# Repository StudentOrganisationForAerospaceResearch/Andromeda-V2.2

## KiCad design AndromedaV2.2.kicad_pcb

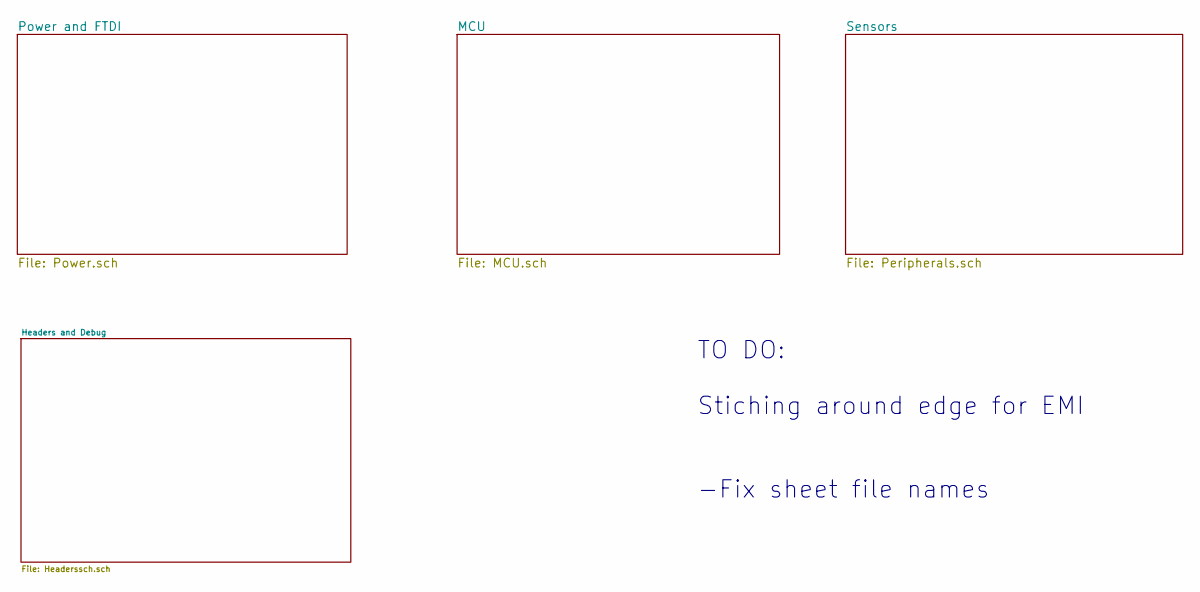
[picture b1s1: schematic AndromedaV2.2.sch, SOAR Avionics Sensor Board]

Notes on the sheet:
TO DO: Stiching around edge for EMI -Fix sheet file names

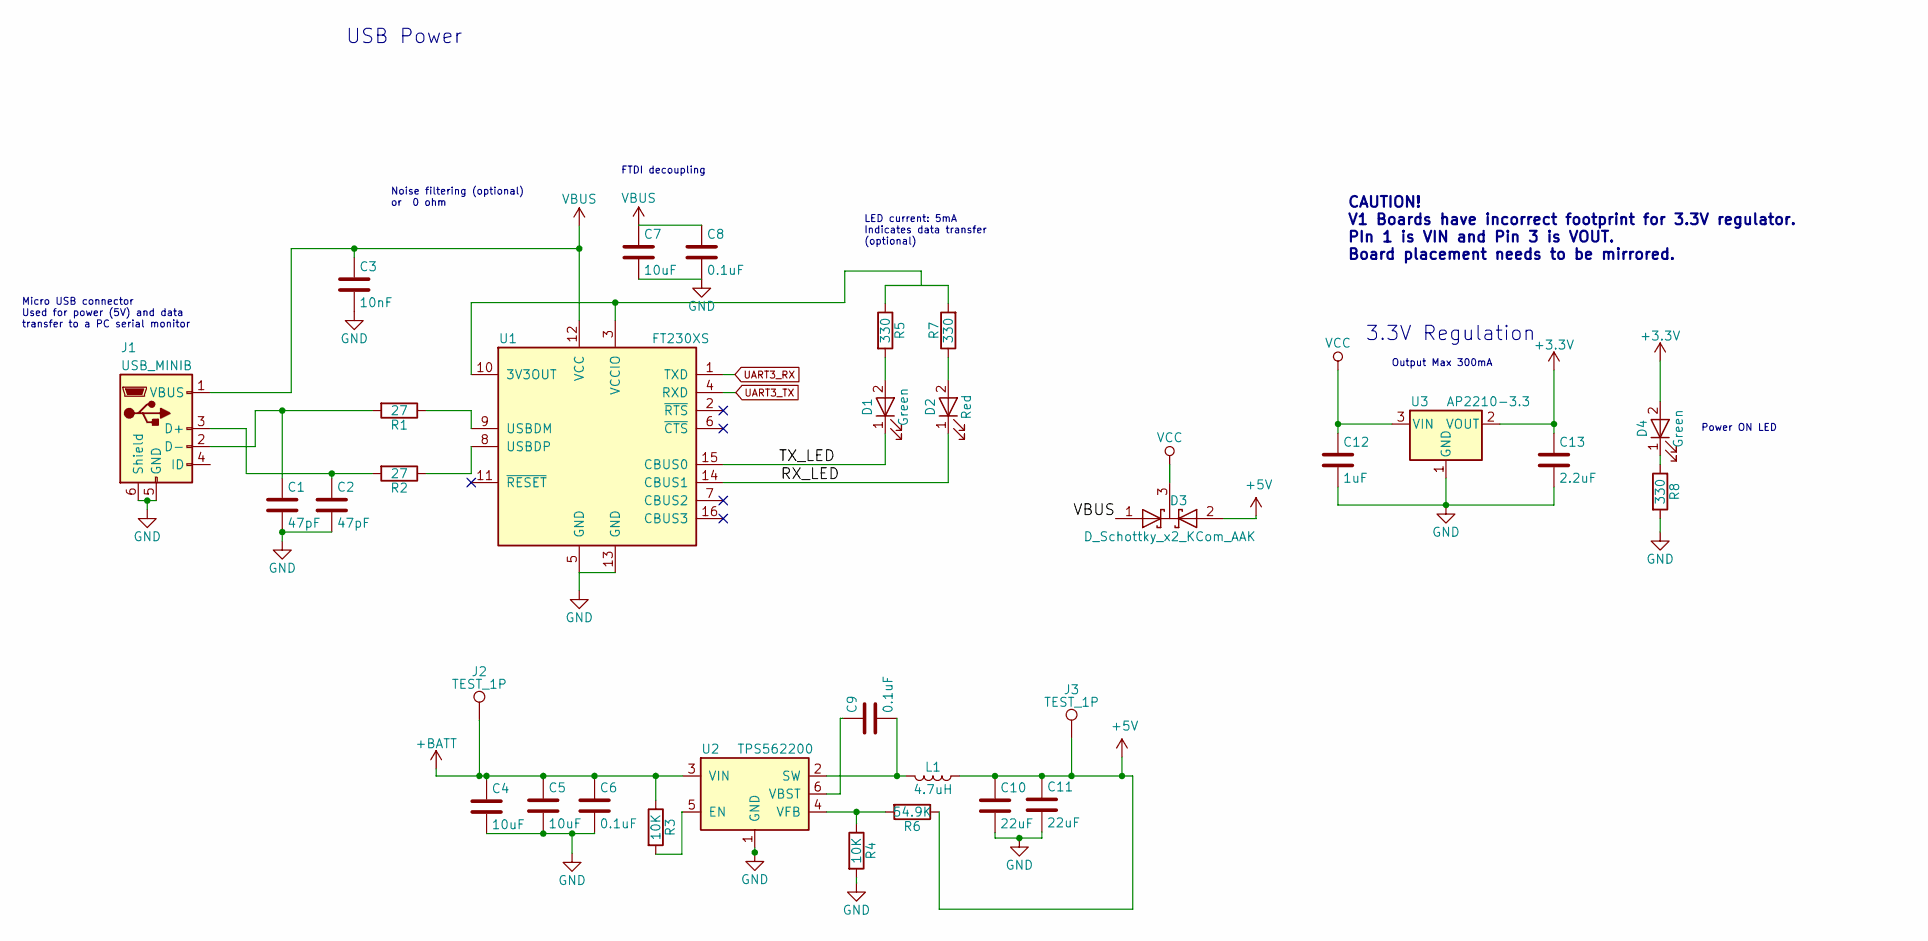
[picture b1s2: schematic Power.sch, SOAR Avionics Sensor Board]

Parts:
C1, C2: 47pF; C_0603
C3: 10nF; C_0603
C4, C5, C7: 10uF; C_0603
C6, C8, C9: 0.1uF; C_0603
C10, C11: 22uF; C_0603
C12: 1uF; C_0603
C13: 2.2uF; C_0603
D1, D4: Green; LED_0805_2012Metric; Digikey LG R971-KN-1
D2: Red; LED_0805_2012Metric; Digikey 475-1278-1-ND
D3: D_Schottky_x2_KCom_AAK; SOT-23; Digikey 1727-5188-1-ND
J1: USB_MINIB; USB-Mini-B; Digikey 690-005-299-043
J2, J3: TEST_1P; Test_Point_Pad_d1.5mm
L1: 4.7uH; L_1008
R1, R2: 27; R_0603
R3, R4: 10K; R_0603
R5, R7, R8: 330; R_0603
R6: 54.9K; R_0603
U1: FT230XS; SSOP-16_3.9x4.9mm_P0.635mm; Digikey 768-1135-1-ND
U2: TPS562200; SOT-23-6
U3: AP2210-3.3; SOT-23

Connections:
+3V3: C13.1, D4.2 (A), U3.2 (VOUT); also elsewhere on the board
+5V: C10.1, C11.1, D3.2 (A), J3.1, L1.1, R6.1; also elsewhere on the board
+BATT: C4.1, C5.1, C6.1, J2.1, R3.1, U2.3 (VIN); also elsewhere on the board
/Power and FTDI/RX_LED: D2.1 (K), U1.14 (CBUS1)
/Power and FTDI/TX_LED: D1.1 (K), U1.15 (CBUS0)
GND: C1.2, C2.2, C3.2, C4.2, C5.2, C6.2, C7.2, C8.2, C10.2, C11.2, C12.2, C13.2, J1.5 (GND), J1.6 (Shield), R4.2, R8.2, U1.5 (GND), U1.13 (GND), U2.1 (GND), U3.1 (GND); also elsewhere on the board
unnamed: C1.1, J1.2 (D-), R1.2
unnamed: C2.1, J1.3 (D+), R2.2
unnamed: C9.1, U2.6 (VBST)
unnamed: C9.2, L1.2, U2.2 (SW)
unnamed: D1.2 (A), R5.2
unnamed: D2.2 (A), R7.1
unnamed: D4.1 (K), R8.1
unnamed: R1.1, U1.9 (USBDM)
unnamed: R2.1, U1.8 (USBDP)
unnamed: R3.2, U2.5 (EN)
unnamed: R4.1, R6.2, U2.4 (VFB)
unnamed: R5.1, R7.2
unnamed: U1.3 (VCCIO), U1.10 (3V3OUT)
UART3_RX: U1.1 (TXD); also elsewhere on the board
UART3_TX: U1.4 (RXD); also elsewhere on the board
VBUS: C3.1, C7.1, C8.1, D3.1 (A), J1.1 (VBUS), U1.12 (VCC)
VCC: C12.1, D3.3 (K), U3.3 (VIN)

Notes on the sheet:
Output Max 300mA
Power ON LED
LED current: 5mA Indicates data transfer (optional)
Micro USB connector Used for power (5V) and data transfer to a PC serial monitor
Noise filtering (optional) or 0 ohm
FTDI decoupling
USB Power
3.3V Regulation
CAUTION! V1 Boards have incorrect footprint for 3.3V regulator. PIn 1 is VIN and Pin 3 is VOUT. Board placement needs to be mirrored.

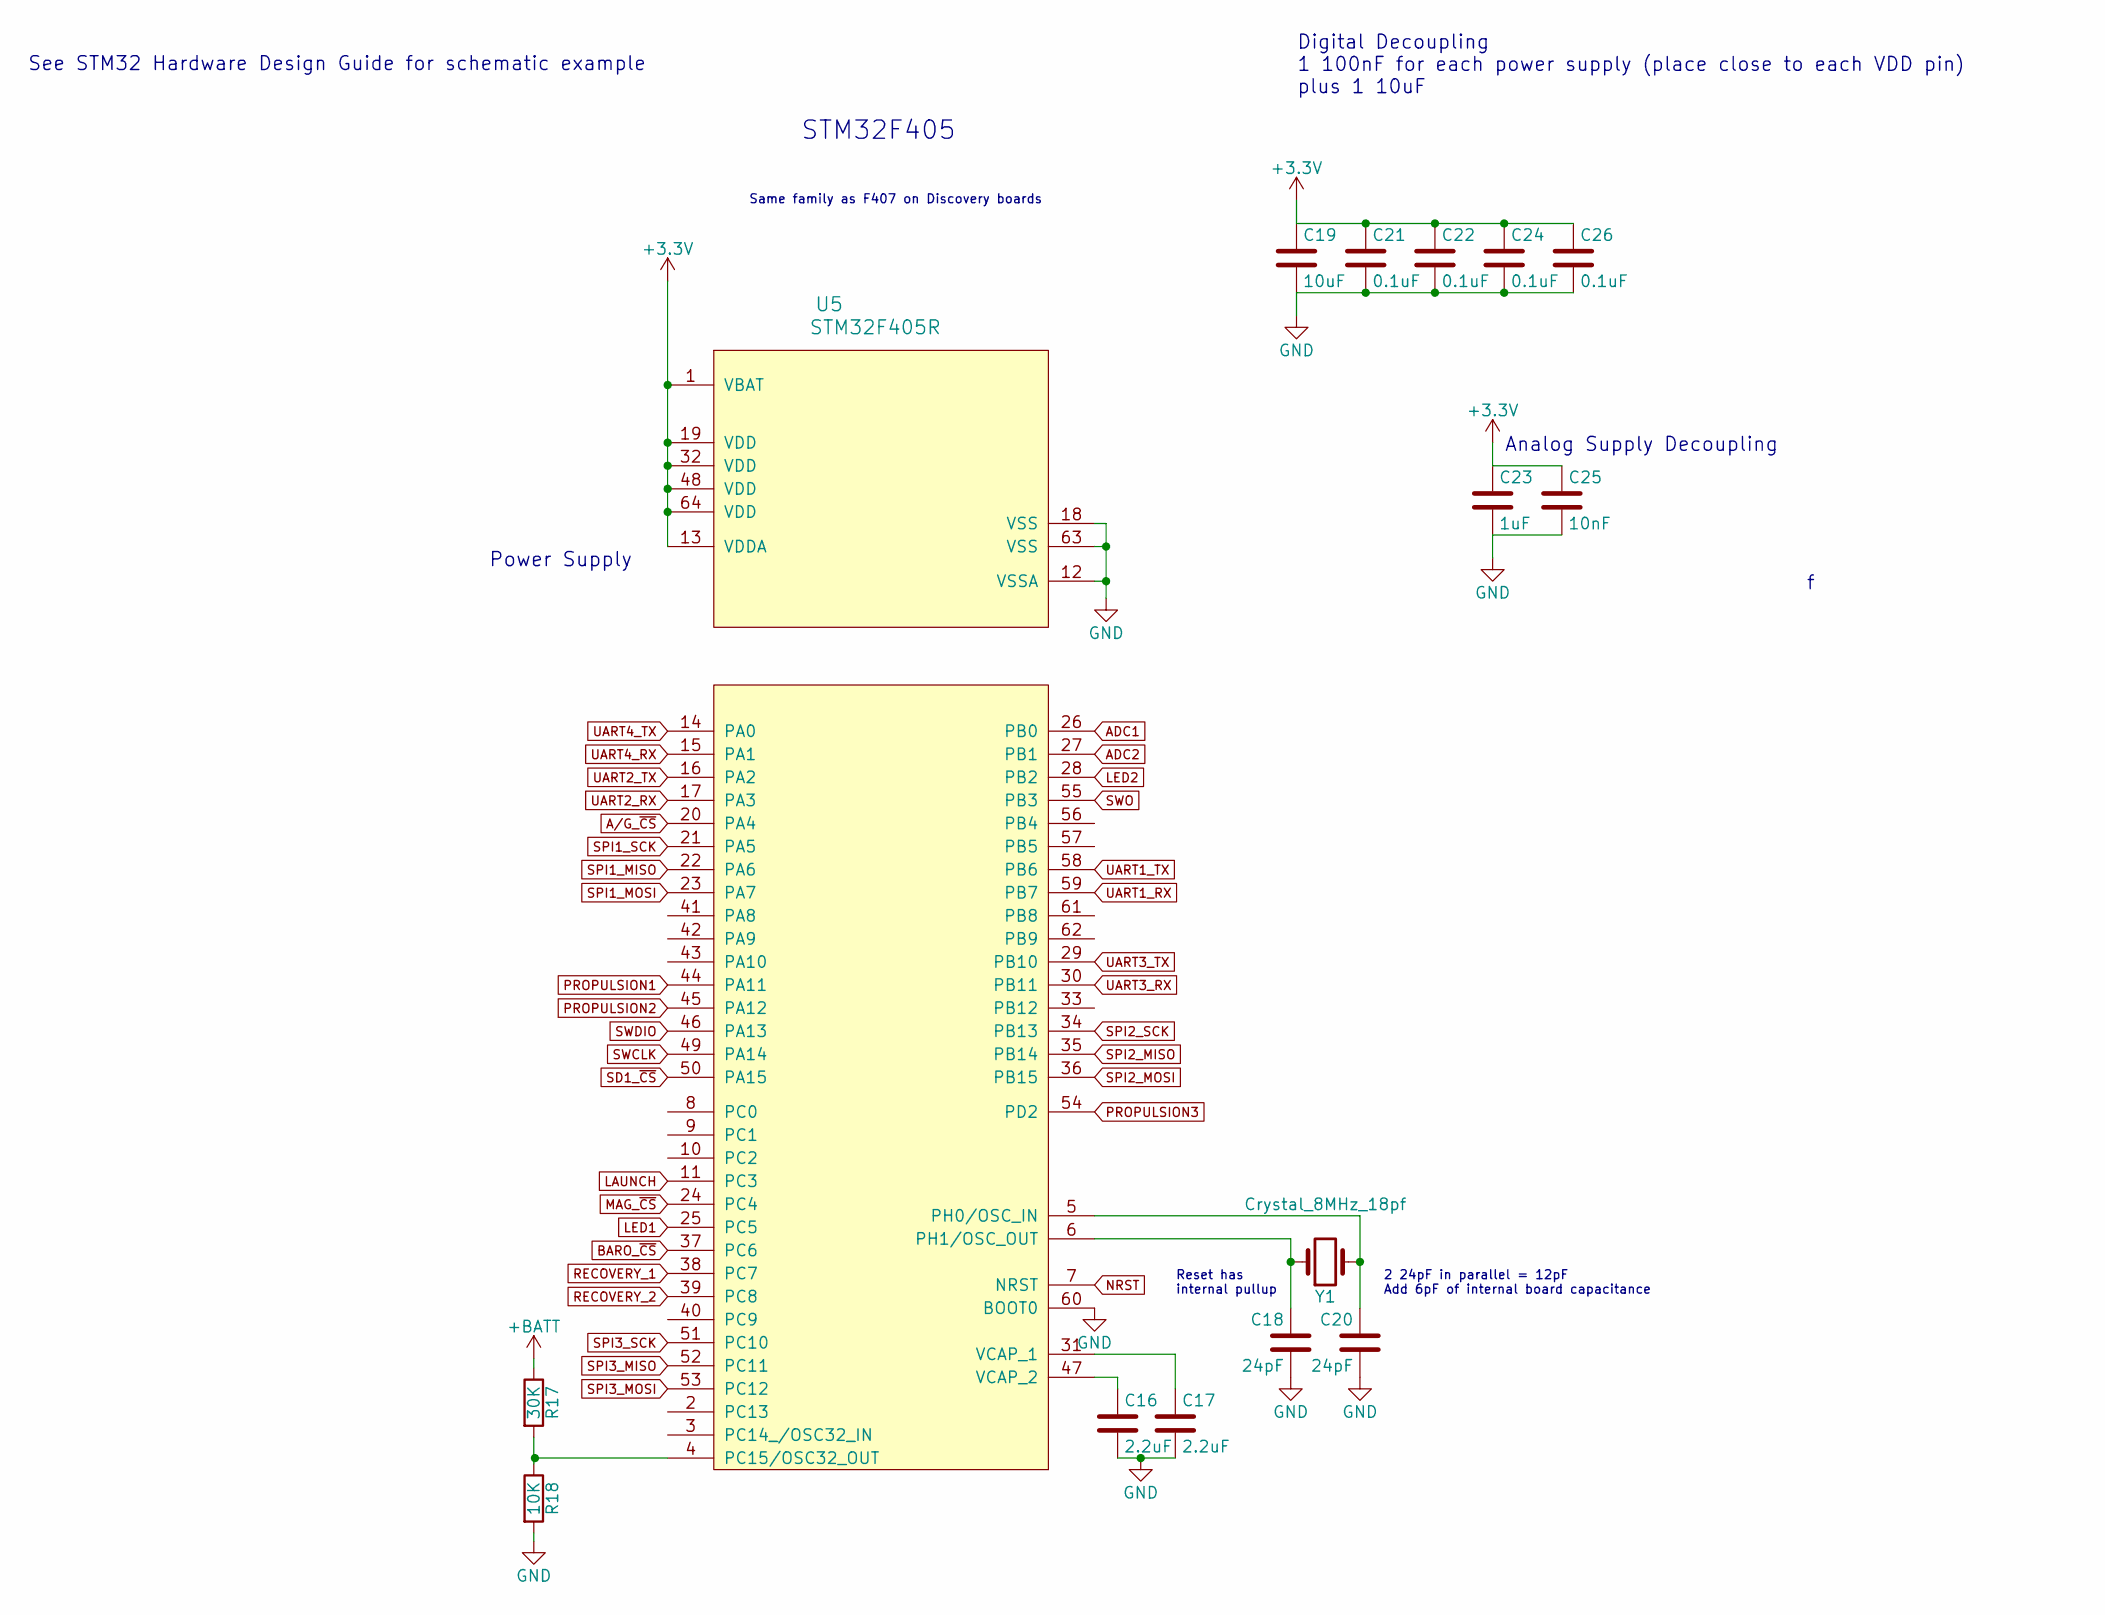
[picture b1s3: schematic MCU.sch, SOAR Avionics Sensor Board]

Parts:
C16, C17: 2.2uF; C_0603
C18, C20: 24pF; C_0603
C19: 10uF; C_0603
C21, C22, C24, C26: 0.1uF; C_0603
C23: 1uF; C_0603
C25: 10nF; C_0603
R17: 30K; R_0603
R18: 10K; R_0603
U5: STM32F405R; LQFP-64_10x10mm_P0.5mm; Digikey 497-11767-ND
Y1: Crystal_8MHz_18pf; Crystal_SMD_HC49-SD; Digikey 535-9089-1-ND

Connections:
+3V3: C19.1, C21.1, C22.1, C23.1, C24.1, C25.1, C26.1, U5.1 (VBAT), U5.13 (VDDA), U5.19 (VDD), U5.32 (VDD), U5.48 (VDD), U5.64 (VDD); also elsewhere on the board
+BATT: R17.1; also elsewhere on the board
A/G_~CS: U5.20 (PA4); also elsewhere on the board
ADC1: U5.26 (PB0); also elsewhere on the board
ADC2: U5.27 (PB1); also elsewhere on the board
BARO_~CS: U5.37 (PC6); also elsewhere on the board
GND: C16.2, C17.2, C18.2, C19.2, C20.2, C21.2, C22.2, C23.2, C24.2, C25.2, C26.2, R18.2, U5.12 (VSSA), U5.18 (VSS), U5.60 (BOOT0), U5.63 (VSS); also elsewhere on the board
LAUNCH: U5.11 (PC3); also elsewhere on the board
LED1: U5.25 (PC5); also elsewhere on the board
LED2: U5.28 (PB2); also elsewhere on the board
MAG_~CS: U5.24 (PC4); also elsewhere on the board
NRST: U5.7 (NRST); also elsewhere on the board
unnamed: C16.1, U5.47 (VCAP_2)
unnamed: C17.1, U5.31 (VCAP_1)
unnamed: C18.1, U5.6 (PH1/OSC_OUT), Y1.1
unnamed: C20.1, U5.5 (PH0/OSC_IN), Y1.2
unnamed: R17.2, R18.1, U5.4 (PC15/OSC32_OUT)
PROPULSION1: U5.44 (PA11); also elsewhere on the board
PROPULSION2: U5.45 (PA12); also elsewhere on the board
PROPULSION3: U5.54 (PD2); also elsewhere on the board
RECOVERY_1: U5.38 (PC7); also elsewhere on the board
RECOVERY_2: U5.39 (PC8); also elsewhere on the board
SD1_~CS: U5.50 (PA15); also elsewhere on the board
SPI1_MISO: U5.22 (PA6); also elsewhere on the board
SPI1_MOSI: U5.23 (PA7); also elsewhere on the board
SPI1_SCK: U5.21 (PA5); also elsewhere on the board
SPI2_MISO: U5.35 (PB14); also elsewhere on the board
SPI2_MOSI: U5.36 (PB15); also elsewhere on the board
SPI2_SCK: U5.34 (PB13); also elsewhere on the board
SPI3_MISO: U5.52 (PC11); also elsewhere on the board
SPI3_MOSI: U5.53 (PC12); also elsewhere on the board
SPI3_SCK: U5.51 (PC10); also elsewhere on the board
SWCLK: U5.49 (PA14); also elsewhere on the board
SWDIO: U5.46 (PA13); also elsewhere on the board
SWO: U5.55 (PB3); also elsewhere on the board
UART1_RX: U5.59 (PB7); also elsewhere on the board
UART1_TX: U5.58 (PB6); also elsewhere on the board
UART2_RX: U5.17 (PA3); also elsewhere on the board
UART2_TX: U5.16 (PA2); also elsewhere on the board
UART3_RX: U5.30 (PB11); also elsewhere on the board
UART3_TX: U5.29 (PB10); also elsewhere on the board
UART4_RX: U5.15 (PA1); also elsewhere on the board
UART4_TX: U5.14 (PA0); also elsewhere on the board

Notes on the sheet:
Reset has internal pullup
Digital Decoupling 1 100nF for each power supply (place close to each VDD pin) plus 1 10uF
Analog Supply Decoupling
See STM32 Hardware Design Guide for schematic example
Power Supply
2 24pF in parallel = 12pF Add 6pF of internal board capacitance
STM32F405
Same family as F407 on Discovery boards

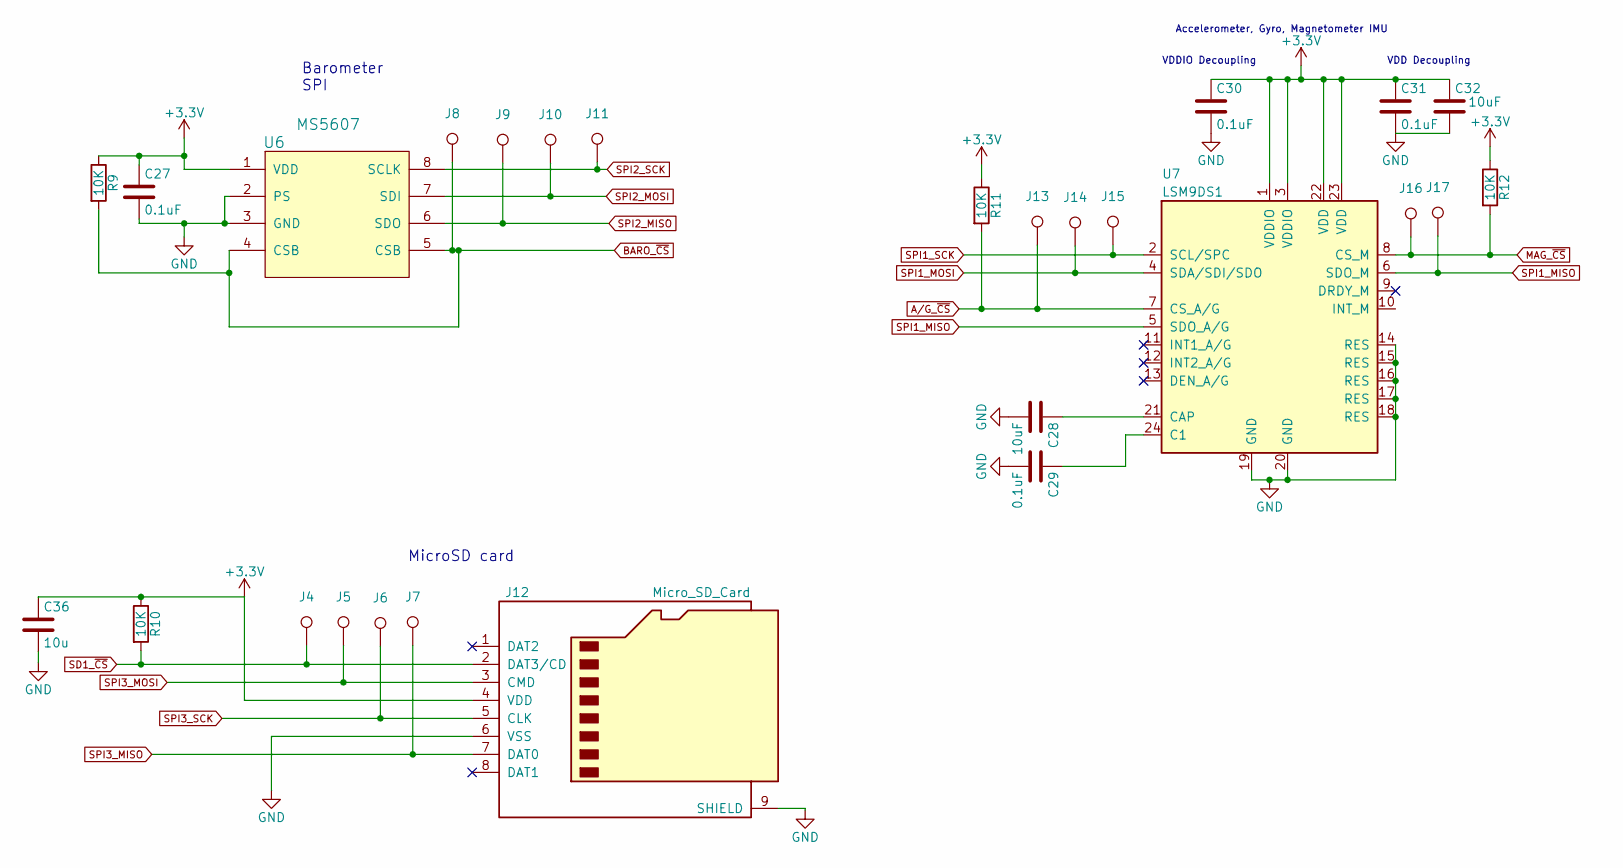
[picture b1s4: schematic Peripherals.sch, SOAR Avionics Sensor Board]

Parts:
C27, C29, C30, C31: 0.1uF; C_0603
C28, C32: 10uF; C_0603
C36: 10u; C_0603
J4, J5, J6, J7, J8, J9, J10, J11, J13, J14, J15, J16, J17: TEST_1P; Test_Point_Pad_d1.5mm
J12: Micro_SD_Card; Hirose_DM3AT-SF-PEJM5_MicroSD; Digikey 0472192001
R9, R10, R11, R12: 10K; R_0603
U6: MS5607; LGA-8_3x5mm_P1.25mm; Digikey MS560702BA03-00
U7: LSM9DS1; LGA-24L_3x3.5mm_P0.43mm; Digikey 497-14946-1-ND

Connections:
+3V3: C27.1, C30.1, C31.1, C32.1, C36.1, J12.4 (VDD), R9.1, R10.1, R11.1, R12.1, U6.1 (VDD), U7.1 (VDDIO), U7.3 (VDDIO), U7.22 (VDD), U7.23 (VDD); also elsewhere on the board
A/G_~CS: J13.1, R11.2, U7.7 (CS_A/G); also elsewhere on the board
BARO_~CS: J8.1, R9.2, U6.4 (CSB), U6.5 (CSB); also elsewhere on the board
GND: C27.2, C28.2, C29.2, C30.2, C31.2, C32.2, C36.2, J12.6 (VSS), J12.9 (SHIELD), U6.2 (PS), U6.3 (GND), U7.14 (RES), U7.15 (RES), U7.16 (RES), U7.17 (RES), U7.18 (RES), U7.19 (GND), U7.20 (GND); also elsewhere on the board
MAG_~CS: J16.1, R12.2, U7.8 (CS_M); also elsewhere on the board
unnamed: C28.1, U7.21 (CAP)
unnamed: C29.1, U7.24 (C1)
SD1_~CS: J4.1, J12.2 (DAT3/CD), R10.2; also elsewhere on the board
SPI1_MISO: J17.1, U7.5 (SDO_A/G), U7.6 (SDO_M); also elsewhere on the board
SPI1_MOSI: J14.1, U7.4 (SDA/SDI/SDO); also elsewhere on the board
SPI1_SCK: J15.1, U7.2 (SCL/SPC); also elsewhere on the board
SPI2_MISO: J9.1, U6.6 (SDO); also elsewhere on the board
SPI2_MOSI: J10.1, U6.7 (SDI); also elsewhere on the board
SPI2_SCK: J11.1, U6.8 (SCLK); also elsewhere on the board
SPI3_MISO: J7.1, J12.7 (DAT0); also elsewhere on the board
SPI3_MOSI: J5.1, J12.3 (CMD); also elsewhere on the board
SPI3_SCK: J6.1, J12.5 (CLK); also elsewhere on the board

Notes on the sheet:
Barometer SPI
VDD Decoupling
VDDIO Decoupling
MicroSD card
Accelerometer, Gyro, Magnetometer IMU

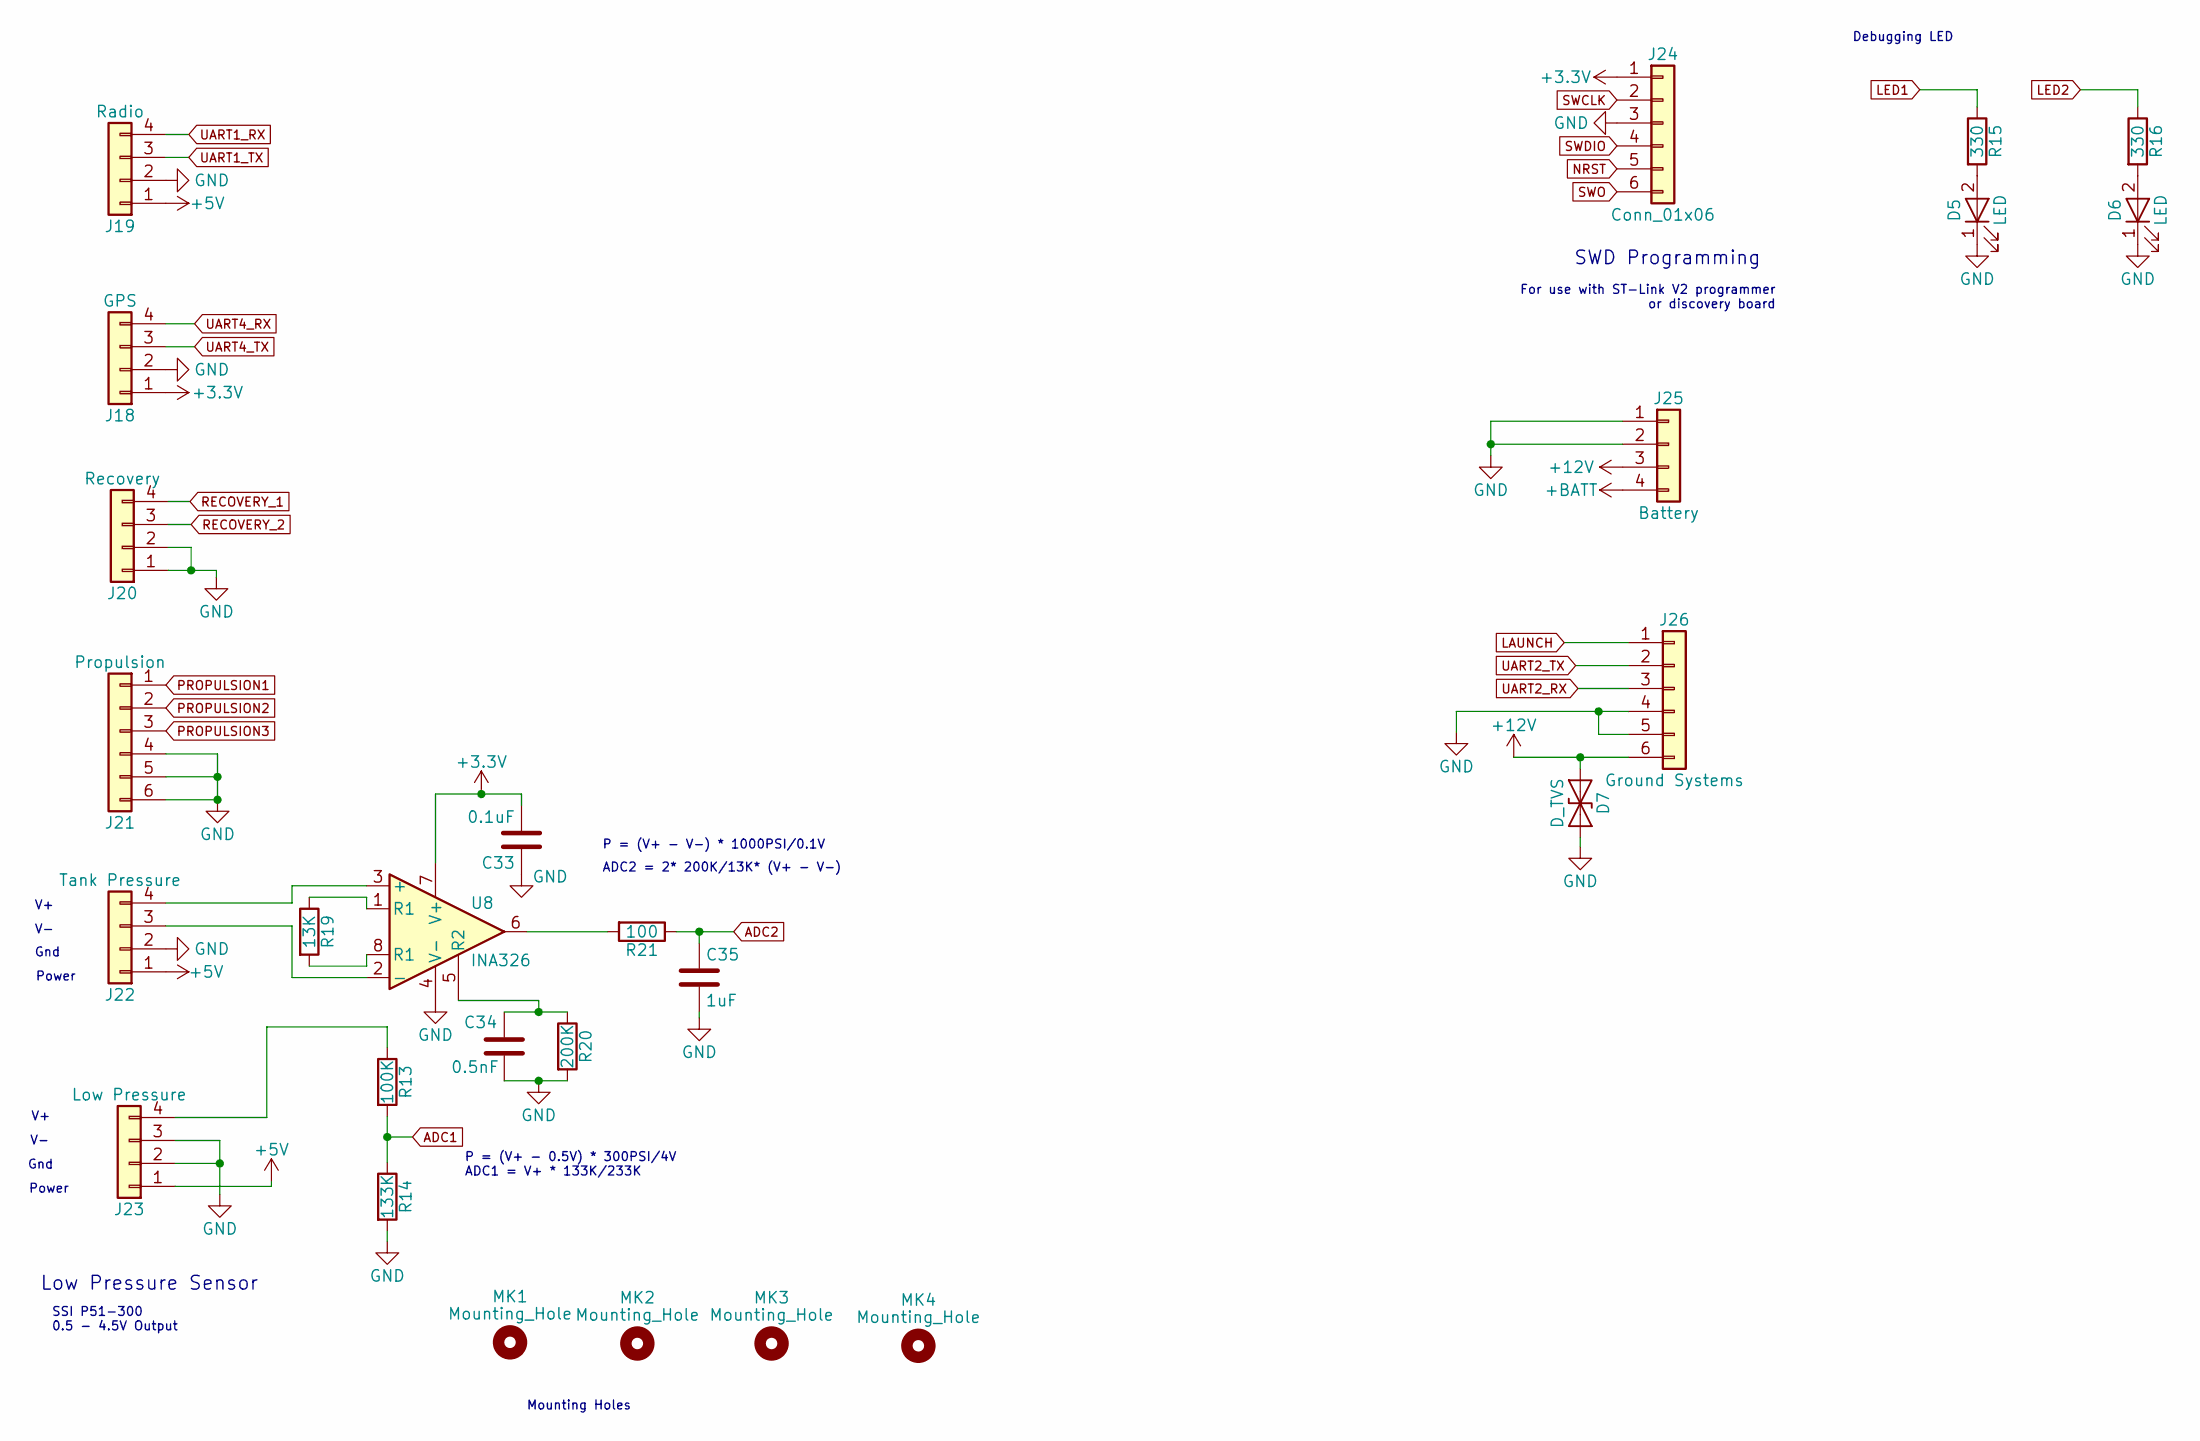
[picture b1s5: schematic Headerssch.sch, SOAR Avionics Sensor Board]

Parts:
C33: 0.1uF; C_0603
C34: 0.5nF; C_0603
C35: 1uF; C_0603
D5, D6: LED; LED_0805_2012Metric
D7: D_TVS; D_SOD-323
J18: GPS; Molex_Micro-Fit_3.0_43045-0400_2x02_P3.00mm_Horizontal
J19: Radio; Molex_Micro-Fit_3.0_43045-0400_2x02_P3.00mm_Horizontal
J20: Recovery; Molex_Micro-Fit_3.0_43045-0400_2x02_P3.00mm_Horizontal
J21: Propulsion; Molex_Micro-Fit_3.0_43045-0600_2x03_P3.00mm_Horizontal
J22: Tank Pressure; Molex_Micro-Fit_3.0_43045-0400_2x02_P3.00mm_Horizontal
J23: Low Pressure; Molex_Micro-Fit_3.0_43045-0400_2x02_P3.00mm_Horizontal
J24: Conn_01x06; PinHeader_1x06_P2.54mm_Vertical
J25: Battery; Molex_Micro-Fit_3.0_43045-0400_2x02_P3.00mm_Horizontal
J26: Ground Systems; Molex_Micro-Fit_3.0_43045-0600_2x03_P3.00mm_Horizontal
MK1, MK2, MK3, MK4: Mounting_Hole; MountingHole_2.5mm_Pad
R13: 100K; R_0603
R14: 133K; R_0603
R15, R16: 330; R_0603
R19: 13K; R_0603
R20: 200K; R_0603
R21: 100; R_0603
U8: INA326; MSOP-8_3x3mm_Pitch0.65mm

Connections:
+3V3: C33.2, J18.1, J24.1, U8.7 (V+); also elsewhere on the board
+5V: J19.1, J22.1, J23.1; also elsewhere on the board
+12V: D7.1 (A1), J25.3, J26.6
+BATT: J25.4; also elsewhere on the board
ADC1: R13.2, R14.1; also elsewhere on the board
ADC2: C35.1, R21.1; also elsewhere on the board
GND: C33.1, C34.2, C35.2, D5.1 (K), D6.1 (K), D7.2 (A2), J18.2, J19.2, J20.1, J20.2, J21.4, J21.5, J21.6, J22.2, J23.2, J23.3, J24.3, J25.1, J25.2, J26.4, J26.5, R14.2, R20.2, U8.4 (V-); also elsewhere on the board
LAUNCH: J26.1; also elsewhere on the board
LED1: R15.1; also elsewhere on the board
LED2: R16.1; also elsewhere on the board
NRST: J24.5; also elsewhere on the board
unnamed: C34.1, R20.1, U8.5 (R2)
unnamed: D5.2 (A), R15.2
unnamed: D6.2 (A), R16.2
unnamed: J22.3, U8.2 (-)
unnamed: J22.4, U8.3 (+)
unnamed: J23.4, R13.1
unnamed: R19.1, U8.1 (R1)
unnamed: R19.2, U8.8 (R1)
unnamed: R21.2, U8.6
PROPULSION1: J21.1; also elsewhere on the board
PROPULSION2: J21.2; also elsewhere on the board
PROPULSION3: J21.3; also elsewhere on the board
RECOVERY_1: J20.4; also elsewhere on the board
RECOVERY_2: J20.3; also elsewhere on the board
SWCLK: J24.2; also elsewhere on the board
SWDIO: J24.4; also elsewhere on the board
SWO: J24.6; also elsewhere on the board
UART1_RX: J19.4; also elsewhere on the board
UART1_TX: J19.3; also elsewhere on the board
UART2_RX: J26.3; also elsewhere on the board
UART2_TX: J26.2; also elsewhere on the board
UART4_RX: J18.4; also elsewhere on the board
UART4_TX: J18.3; also elsewhere on the board

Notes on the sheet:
SWD Programming
For use with ST-Link V2 programmer or discovery board
Debugging LED
Mounting Holes
Low Pressure Sensor
Power
Gnd
SSI P51-300 0.5 - 4.5V Output
P = (V+ - 0.5V) * 300PSI/4V ADC1 = V+ * 133K/233K
ADC2 = 2* 200K/13K* (V+ - V-)
P = (V+ - V-) * 1000PSI/0.1V

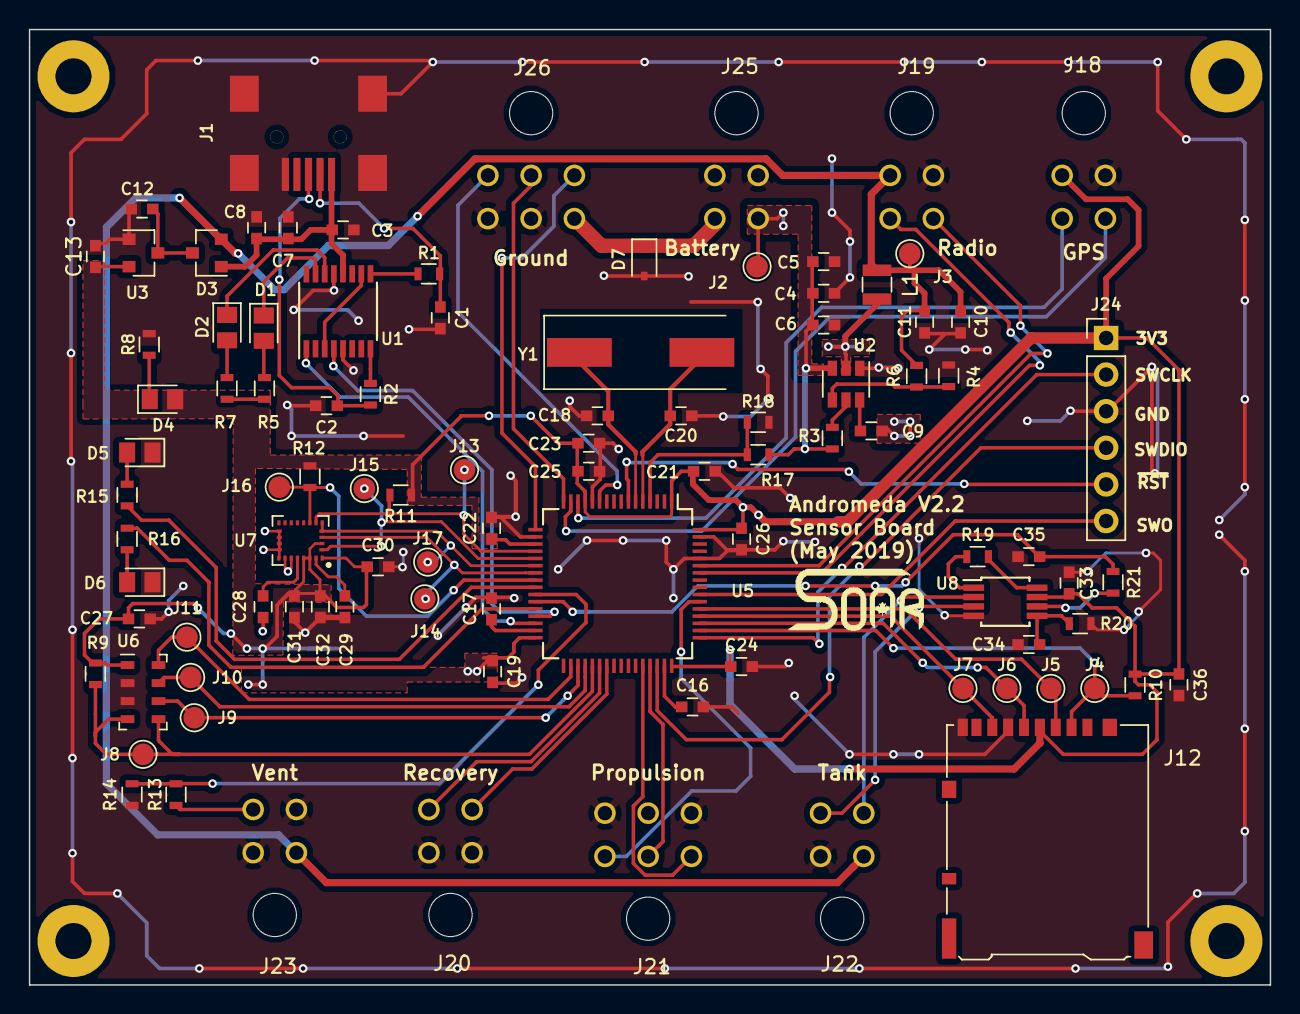
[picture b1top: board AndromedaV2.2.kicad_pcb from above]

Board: 2 copper layers, 86.1 x 66.3 mm, 102 parts (0 on the bottom side), 73 nets.

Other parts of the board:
LOGO_SOAR: LOGO_SOAR
